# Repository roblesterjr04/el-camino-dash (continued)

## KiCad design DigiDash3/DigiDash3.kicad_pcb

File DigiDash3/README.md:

# DigiDash main board, rev 3: all through-hole

Rev 2 ([`DigiDash2/`](../DigiDash2/)) with every SMD part swapped for a through-hole one, so the board needs **no
assembly service**: order the bare PCB and solder it by hand (about 170 parts, all leaded). Same outline, slot row,
screen headers, mounting and screen holes and rear connector group as rev 2, so the housing fits both. Started
2026-10-26 to get the first set under the fab's assembly fees and the 35 % US duty on assembled boards.

| File | What |
| --- | --- |
| `DigiDash3.kicad_sch` / `.kicad_pcb` / `.kicad_pro` | The board: 329 × 113 mm, **2 layers**, parts on the back, screen headers on the front. KiCad 10 |
| `DigiDash3.pretty/` | The slot socket (numbered to mate with the cards) and a radial PTC footprint, from `generate/gen_footprints.py` |
| `DigiDash3_BOM.csv` | Parts list for hand assembly (`generate/gen_bom.py`): grouped by vendor (DigiKey, then LCSC), with each line's product link and its unit price at quantity 1 where the page showed one (looked up 2026-10-26; `SOURCE` in the generator) |
| `fab/` | Gerbers, drill, placement files (`python3 ../tools/fab_export.py DigiDash3`) |
| `generate/` | The generators, from rev 2's: `gen_sch.py` (schematic), `gen_pcb.py` (placement + Freerouting), `gen_bom.py`, `drc.py` |

**Firmware:** none on the board itself. The three screens run [`firmware/esp32_p4_display`](../firmware/esp32_p4_display/), as on rev 2.

## What changed from rev 2

| Block | Rev 2 (SMD) | Rev 3 (through-hole) |
| --- | --- | --- |
| 5 V | One TPS54560B, 5 A, 400 kHz | **Two LM2576HV-5.0** (TO-220-5 lying flat, 3 A, 52 kHz): U2 feeds the three screens (`+5V_SCR`), U3 feeds the board, the six slots and the cable ports (`+5V`). Each: 100 µF 63 V in, SB560 catch diode, **68 µH** radial inductor (Abracon AIAP-03-680K, 3.3 A: no stocked 100 µH part of 3 A or more fits a 14 mm / 10 mm-pitch footprint, and 68 µH costs about 45 % more ripple current at this load, still continuous), 1000 µF 16 V out (TI SNVS107 figure 1) |
| Enable | EN divider from the ignition, WAKE through a BAT54S | Both bucks' ON/OFF pins on one 2N3904 (Q7): low (on) while the ignition is on (47k) or a card holds WAKE (1N4148 + 10k). Off, the pins rest at 12V_BATT through 100k (ON/OFF may go to VIN) |
| 3.3 V | AP7361C-33 SOT-223 | LD1117V33, TO-220 lying flat, 10 µF electrolytics in and out. Also feeds the video module when JP1 is strapped to 3.3 V |
| 1.8 V | AP2112K-1.8 for the TVP5150 core | Gone with the decoder |
| Reverse / switch FETs | SUD50P04 DPAK ×3 | IRF4905 TO-220 lying flat ×3 (55 V, 20 mΩ), gates clamped by 1N4744A (15 V) |
| TVS | SMCJ33A ×2 | 1.5KE33A (DO-201) ×2 |
| CAN transceivers | MCP2562-E/SN SOIC ×3 | **MCP2562-E/P DIP-8** ×3 (same pins) |
| CAN ESD clamps | NUP2105L SOT-23 ×2 | Two SA24CA bidirectional TVS (DO-15) per site: CANH and CANL to ground |
| Clamps / wake diode | BAT54S ×3 | BAT85 (DO-35) ×4, 1N4148 ×1 |
| PTCs | 1812 / 1206 SMD ×35 | Bourns MF-R radial ×29 (MF-R050, R110, R010, R020; same hold currents, 60 V except the 1.1 A at 30 V) |
| Video | TVP5150AM1 on the board, crystal, RCA input chain | **J8: a 2×10 socket for a TVP5150 breakout module**, JP1 (its VCC: 5 V or 3.3 V), J10 (PCLK / RESET wires). The module carries its own video input, crystal and regulators, so J11 (RCA) and the input chain are gone |
| Termination switch | KingTek SMD | Through-hole 2-way slide DIP (DSWB02LHGET) |
| Passives | 0603 / 0805 / 1210 | 1/4 W axial resistors (7.62 mm), 5 mm disc 100 nF, radial electrolytics |
| Layers | 4 (GND and +5 V planes) | **2**, ground pours on both sides; 0.25 mm tracks, 0.15 mm clearance, 0.6 / 0.3 vias (JLCPCB's 2-layer limit is 0.127 / 0.127); the 5 V feeds at 1.5 mm, 12 V at 1.0 mm. The slot sockets' pads are 1.5 mm on 1.0 mm holes (rev 2: 1.7), so two tracks pass between neighbours: at 0.3 / 0.2 and 1.7 mm pads the router left bus nets open |

Unchanged: J7 / J13 / J9 / J6 / J16 / J27 / J17–J25 and their pin use, the six slot sockets and their pinout
([`accessory_ports.md`](../docs/hardware/accessory_ports.md)), the AUX 12 V path, the sensor-serial fan-out, the
illumination / reverse inputs, the slot ID resistors, WAKE, LAMP / REV levels, the audio bus and I2S rail, and the
screen headers' pin use (`HDR_NETS` in `gen_sch.py`, with `+5V_SCR` on pins 1 and 3).

## The video module socket (J8)

J8's pin order is the module's own, odd pins in one row, even in the other, 1–20:

| Pin | Net | Pin | Net |
| --- | --- | --- | --- |
| 1 | VID_VCC (JP1: 5 V or 3.3 V) | 2 | GND |
| 3 | CL_SCL (cluster I2C) | 4 | CL_SDA |
| 5 | V_VS → J1 pin 24 | 6 | V_HS → J1 pin 30 |
| 7 | n.c. | 8 | n.c. |
| 9 | V_D7 → J1 pin 16 | 10 | V_D6 → J1 pin 32 |
| 11 | V_D5 → J1 pin 35 | 12 | V_D4 → J1 pin 39 |
| 13 | V_D3 → J1 pin 8 | 14 | V_D2 → J1 pin 11 |
| 15 | V_D1 → J1 pin 12 | 16 | V_D0 → J1 pin 14 |
| 17 | n.c. | 18 | V_FID → J1 pin 37 |
| 19 | INT (10k to ground, unused) | 20 | ID (10k to ground, **not fitted**: only if the module wants its address strap here) |

**The module's header has no pixel-clock pin.** The center screen's camera interface needs PCLK (J1 pin 25), so J10
pin 1 carries that net: run a wire from the module's PCLK point (a test pad or the decoder's SCLK pin) to J10 pin 1.
J10 pin 2 is the center screen's reset line (GPIO52, J1 pin 36) for the module's RESET if it has one; pin 3 is GND.
Check the module's supply before strapping JP1: most TVP5150 breakouts take 3.3 V. Fit a **female** 2×10 socket at
J8 (the module carries the pins; the BOM says so).

## Board

- **Sides:** every part's body is on the back; only the three screen headers are on the front. Soldering is from
  the front (the pin tails come through there), so the screens come off first.
- **Heights on the back, outside the cards:** rev 2's housing allowed about 10.5 mm over the power section. Rev 3's
  power parts are taller: the inductors (Abracon AIAP-03-680K, 11.4 mm across) stand **23 mm**, the tallest parts on the board; the 1000 µF output caps (Rubycon 16YXJ1000MT810X16) 16 mm;
  the 100 µF caps 12.5 mm; the radial PTCs 8–9 mm; the TO-220s lying flat about 5 mm; the DIP transceivers 4 mm. The
  video module on J8 stands about 12 mm plus its own height. **The housing's power-section step needs to grow to
  about 25 mm over the two inductors (18 mm elsewhere)**, and the module's footprint (about 40 × 30 mm, at x 190–220, y 60–80) needs room behind J8.
- **Under the cards** (7 mm limit) only lying-flat resistors, diodes, DIPs and TO-92s go; the placer keeps the tall
  parts out of the card envelopes (`TALL_RE` in `gen_pcb.py`).
- **Placement:** slots, screen headers, holes and the rear connector group as rev 2 (`SLOTS`, `SCREENS`, `HOLES_MH`,
  `GROUP`). The two bucks lie flat at x 170, y 44 and 60, pins toward the slots; Q5 and the LDO east of them; the
  video socket below the power section at (205, 69); the transceivers beside their headers.

## Status

**Schematic: done** (168 parts, 2026-10-26). **PCB: placed, routed and DRC-clean** (2026-10-26): Freerouting at
150 passes, 2083 tracks and vias, then **two links drawn by hand** that the finisher would not make because they end
on the net ties' pads (its clearance check keeps everything off a tie): AUDIO_GND from its F.Cu run at y 63.42 up to
NT2 pad 2 (91.75, 61.85), and AUX_GND on B.Cu, 1.0 mm, from (249.65, 64.0) down to NT1 pad 2 (249.65, 71.5).
**A regeneration drops those two** (re-add them, or check the DRC's two unconnected items). DRC: 0 errors; the
expected warnings are the two library-mismatch notes and two silkscreen overlaps. Fab files exported. The inductors' leads are bent out to the 10 mm pads (the Abracon's own pitch is narrower); the body sits
above the pads. Not yet checked: the LM2576 layout by eye (each buck's input cap,
catch diode and inductor should sit tight round its pins), the housing against the heights above, and the module's
PCLK / RESET / VCC against the actual breakout.

## Regenerating

KiCad 10, numpy in KiCad's python, Freerouting 1.9.0 (the jar in `../DigiDash2/generate/`) on Java 17+:

```bash
KIPY=/Applications/KiCad/KiCad.app/Contents/Frameworks/Python.framework/Versions/Current/bin/python3
python3 generate/gen_footprints.py && python3 generate/gen_sch.py   # also writes generate/refs.json
JAVA=/opt/homebrew/opt/openjdk@17/bin/java FR_PASSES=60 $KIPY generate/gen_pcb.py --route ../DigiDash2/generate/freerouting-1.9.0.jar
python3 generate/drc.py && $KIPY generate/gen_bom.py && python3 ../tools/fab_export.py DigiDash3
```

With no planes there is no fan-out or stitching step: Freerouting routes GND like any other net, and the ground pours
are filled afterwards. `--from-ses`, `--finish`, `--fill` and `--labels` work as on rev 2. Do not set `DIGIDASH_RIPUP=1`
on this board: the rip-up finisher cascaded for over an hour without ending (2026-10-26).

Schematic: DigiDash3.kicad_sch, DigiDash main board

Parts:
C1, C3, C5, C10: 100u 63V; CP_Radial_D10.0mm_P5.00mm
C2, C9, C11, C12, C13, C14, C15, C16, C17, C18, C19, C20, C21: 100n; C_Disc_D5.0mm_W2.5mm_P5.00mm
C4, C6: 1000u 16V; CP_Radial_D10.0mm_P5.00mm
C7, C8: 10u 25V; CP_Radial_D5.0mm_P2.00mm
D4, D8, D9: 1N4744A; D_DO-41_SOD81_P10.16mm_Horizontal
D5, D10: 1.5KE33A; D_DO-201AD_P15.24mm_Horizontal
D6, D7: SB560; D_DO-201AD_P15.24mm_Horizontal
D11, D12, D13, D14: SA24CA; D_DO-15_P10.16mm_Horizontal
D15: 1N4148; D_DO-35_SOD27_P7.62mm_Horizontal
D16, D17, D18, D19: BAT85; D_DO-35_SOD27_P7.62mm_Horizontal
F1: 5A mini blade; Fuseholder_Blade_Mini_Keystone_3568
F2, F4, F5, F6, F7, F9, F10, F13, F14, F17, F18, F21, F22, F25, F26, F29, F30: PTC 0.5A; PTC_Radial_P5.08mm
F3, F11, F15, F19, F23, F27, F31: PTC 0.1A; PTC_Radial_P5.08mm
F8: PTC 1.1A; PTC_Radial_P5.08mm
F12, F16, F20, F24, F28, F32: PTC 0.2A; PTC_Radial_P5.08mm
H1, H2, H3, H4: MountingHole; MountingHole_3.2mm_M3_Pad
J1: Center Screen - Master; PinHeader_2x20_P2.54mm_Vertical
J4: Right Screen; PinHeader_2x20_P2.54mm_Vertical
J5: Left Screen; PinHeader_2x20_P2.54mm_Vertical
J6: Serial; JST_PH_B4B-PH-K_1x04_P2.00mm_Vertical
J7: Vehicle power; Molex_Micro-Fit_3.0_43650-0615_1x06_P3.00mm_Vertical
J8: Video module; PinHeader_2x10_P2.54mm_Vertical
J9: Backup Camera; JST_PH_B4B-PH-K_1x04_P2.00mm_Vertical
J10: Video aux; PinHeader_1x03_P2.54mm_Vertical
J13: AUX 12V in; Molex_Mini-Fit_Jr_5566-02A_2x01_P4.20mm_Vertical
J16: CAN debug; PinHeader_1x03_P2.54mm_Vertical
J17: Cable port 1; JST_PH_B4B-PH-K_1x04_P2.00mm_Vertical
J22: Cable port 2; JST_PH_B4B-PH-K_1x04_P2.00mm_Vertical
J23: Cable port 3; JST_PH_B4B-PH-K_1x04_P2.00mm_Vertical
J24: Cable port 4; JST_PH_B4B-PH-K_1x04_P2.00mm_Vertical
J25: Trunk port; Molex_Micro-Fit_3.0_43650-0415_1x04_P3.00mm_Vertical
J27: Sensor serial in; PinHeader_1x02_P2.54mm_Vertical
J31: Slot 1; Slot_Socket_2x15_P2.54mm_Vertical
J32: Slot 2; Slot_Socket_2x15_P2.54mm_Vertical
J33: Slot 3; Slot_Socket_2x15_P2.54mm_Vertical
J34: Slot 4; Slot_Socket_2x15_P2.54mm_Vertical
J35: Slot 5; Slot_Socket_2x15_P2.54mm_Vertical
J36: Slot 6; Slot_Socket_2x15_P2.54mm_Vertical
JP1: Video VCC; PinHeader_1x03_P2.54mm_Vertical
L1, L2: 68u; L_Radial_D14.2mm_P10.00mm_Neosid_SD14
NT1, NT2: NetTie; NetTie-2_THT_Pad1.0mm
Q1, Q3, Q4, Q7: 2N3904; TO-92_Inline
Q2, Q5, Q6: IRF4905; TO-220-3_Horizontal_TabDown
R1, R5, R6, R9, R10, R13, R14, R15, R20, R21, R22, R23, R24, R26, R28, R30: 10k; R_Axial_DIN0207_L6.3mm_D2.5mm_P7.62mm_Horizontal
R2, R38, R39, R41: 100k; R_Axial_DIN0207_L6.3mm_D2.5mm_P7.62mm_Horizontal
R3, R37: 47k; R_Axial_DIN0207_L6.3mm_D2.5mm_P7.62mm_Horizontal
R4, R8, R36: 22k; R_Axial_DIN0207_L6.3mm_D2.5mm_P7.62mm_Horizontal
R7, R18, R19: 4.7k; R_Axial_DIN0207_L6.3mm_D2.5mm_P7.62mm_Horizontal
R11, R12, R32: 1k; R_Axial_DIN0207_L6.3mm_D2.5mm_P7.62mm_Horizontal
R16, R17: 120; R_Axial_DIN0207_L6.3mm_D2.5mm_P7.62mm_Horizontal
R25, R27, R29: 20k; R_Axial_DIN0207_L6.3mm_D2.5mm_P7.62mm_Horizontal
R31: 10k; R_Axial_DIN0207_L6.3mm_D2.5mm_P7.62mm_Horizontal; not fitted
R33: 3.3k; R_Axial_DIN0207_L6.3mm_D2.5mm_P7.62mm_Horizontal
R34: 6.8k; R_Axial_DIN0207_L6.3mm_D2.5mm_P7.62mm_Horizontal
R35: 12k; R_Axial_DIN0207_L6.3mm_D2.5mm_P7.62mm_Horizontal
R40, R42: 27k; R_Axial_DIN0207_L6.3mm_D2.5mm_P7.62mm_Horizontal
SW1: TERM; SW_DIP_SPSTx02_Slide_6.7x6.64mm_W7.62mm_P2.54mm_LowProfile
U2, U3: LM2576HVT-5.0; TO-220-5_Horizontal_TabDown
U5, U9, U10: MCP2562-E/P; DIP-8_W7.62mm
U11: LD1117V33; TO-220-3_Horizontal_TabDown

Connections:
+3V3: C8.1, C9.1, C12.1, C14.1, C16.1, D16.1 (K), D18.1 (K), F3.1, F11.1, F15.1, F19.1, F23.1, F27.1, F31.1, JP1.3, R13.1, R14.1, R15.1, R18.1, R19.1, U5.5 (Vio), U9.5 (Vio), U10.5 (Vio), U11.2 (VO)
+5V: C6.1, C7.1, C11.1, C13.1, C15.1, F4.1, F5.1, F6.1, F7.1, F9.1, F13.1, F17.1, F21.1, F25.1, F29.1, JP1.1, L2.2, U3.4 (FB), U5.3 (VDD), U9.3 (VDD), U10.3 (VDD), U11.3 (VI)
/3V3_R: J4.18, R12.2
/12V_BATT: C1.1, C2.1, C3.1, C5.1, D4.1 (K), D5.1 (A1), D8.1 (K), F12.1, F16.1, F20.1, F24.1, F28.1, F32.1, Q2.3 (S), Q5.3 (S), R2.1, R6.1, U2.1 (VIN), U3.1 (VIN)
/+5V_SCR: C4.1, J1.1, J1.3, J4.1, J4.3, J5.1, J5.3, L1.2, U2.4 (FB)
/AUDIO_GND: J31.23, J32.23, J33.23, J34.23, J35.23, J36.23, NT2.2 (B)
/AUDIO_L: J31.21, J32.21, J33.21, J34.21, J35.21, J36.21
/AUDIO_R: J31.22, J32.22, J33.22, J34.22, J35.22, J36.22
/AUX12: C10.1, D9.1 (K), D10.1 (A1), J31.25, J31.26, J31.27, J32.25, J32.26, J32.27, J33.25, J33.26, J33.27, J34.25, J34.26, J34.27, J35.25, J35.26, J35.27, J36.25, J36.26, J36.27, Q6.3 (S)
/AUX_GND: C10.2, D10.2 (A2), J13.2, J31.28, J31.29, J31.30, J32.28, J32.29, J32.30, J33.28, J33.29, J33.30, J34.28, J34.29, J34.30, J35.28, J35.29, J35.30, J36.28, J36.29, J36.30, NT1.2 (B), R10.2
/AUX_IN: F1.1, J13.1
/AUX_IN_F: F1.2, Q6.2 (D)
/BATT_IN: J7.1, J7.2, Q2.2 (D)
/BUCK_ONOFF: Q7.3 (C), R2.2, U2.5 (~ON/OFF), U3.5 (~ON/OFF)
/C1_5V: F4.2, J17.1
/C2_5V: F5.2, J22.1
/C3_5V: F6.2, J23.1
/C4_5V: F7.2, J24.1
/CAM_12V: F2.2, J9.2
/CANH: D11.1 (A1), D13.1 (A1), J16.1, J17.2, J22.2, J23.2, J24.2, J25.1, J31.5, J32.5, J33.5, J34.5, J35.5, J36.5, R16.1, R17.1, U5.7 (CANH), U9.7 (CANH), U10.7 (CANH)
/CANL: D12.1 (A1), D14.1 (A1), J16.2, J17.3, J22.3, J23.3, J24.3, J25.2, J31.6, J32.6, J33.6, J34.6, J35.6, J36.6, R16.2, SW1.4, U5.6 (CANL), U9.6 (CANL), U10.6 (CANL)
/CAN_RX_C: J1.23, U9.4 (RXD)
/CAN_RX_L: J5.23, U5.4 (RXD)
/CAN_RX_R: J4.23, U10.4 (RXD)
/CAN_TERM_R: R17.2, SW1.1
/CAN_TX_C: J1.31, R14.2, U9.1 (TXD)
/CAN_TX_L: J5.31, R13.2, U5.1 (TXD)
/CAN_TX_R: J4.31, R15.2, U10.1 (TXD)
/CL_SCL: J1.34, J4.34, J5.34, J8.3, R19.2
/CL_SDA: J1.38, J4.38, J5.38, J8.4, R18.2
/I2S_BCK: J31.15, J32.15, J33.15, J34.15, J35.15, J36.15
/I2S_MCLK: J31.24, J32.24, J33.24, J34.24, J35.24, J36.24
/I2S_MIC: J31.17, J32.17, J33.17, J34.17, J35.17, J36.17
/I2S_RET: J31.18, J32.18, J33.18, J34.18, J35.18, J36.18
/I2S_WS: J31.16, J32.16, J33.16, J34.16, J35.16, J36.16
/IGN_IN: J7.5, R3.1, R8.1
/ILLUM_IN: J7.6, R20.1, R39.1
/Illumination: C17.1, J1.28, Q1.3 (C)
/LAMP_LVL: C20.1, D16.2 (A), D17.1 (K), J31.13, J32.13, J33.13, J34.13, J35.13, J36.13, R39.2, R40.1
/POS_L: J5.17, R11.1
/POS_R: J4.17, R12.1
/Q1_B: Q1.2 (B), R20.2, R21.1
/Q2_G: D4.2 (A), Q2.1 (G), R1.1
/Q3_B: Q3.2 (B), R22.2, R23.1
/Q4_B: Q4.2 (B), R8.2, R9.1
/Q4_C: Q4.3 (C), R7.2
/Q5_G: D8.2 (A), Q5.1 (G), R6.2, R7.1
/Q6_G: D9.2 (A), Q6.1 (G), R10.1
/Q7_B: Q7.2 (B), R3.2, R4.1, R5.2
/REV_IN: J9.1, R22.1, R41.1
/REV_LVL: C21.1, D18.2 (A), D19.1 (K), J31.14, J32.14, J33.14, J34.14, J35.14, J36.14, R41.2, R42.1
/REV_TRIGGER: C18.1, J1.27, Q3.3 (C)
/S1_3V3: F11.2, J31.9
/S1_5V: F9.2, J31.1, J31.2
/S1_12V: F10.2, J31.8
/S1_BATT: F12.2, J31.10
/S1_ID: J31.11, R32.1
/S2_3V3: F15.2, J32.9
/S2_5V: F13.2, J32.1, J32.2
/S2_12V: F14.2, J32.8
/S2_BATT: F16.2, J32.10
/S2_ID: J32.11, R33.1
/S3_3V3: F19.2, J33.9
/S3_5V: F17.2, J33.1, J33.2
/S3_12V: F18.2, J33.8
/S3_BATT: F20.2, J33.10
/S3_ID: J33.11, R34.1
/S4_3V3: F23.2, J34.9
/S4_5V: F21.2, J34.1, J34.2
/S4_12V: F22.2, J34.8
/S4_BATT: F24.2, J34.10
/S4_ID: J34.11, R35.1
/S5_3V3: F27.2, J35.9
/S5_5V: F25.2, J35.1, J35.2
/S5_12V: F26.2, J35.8
/S5_BATT: F28.2, J35.10
/S5_ID: J35.11, R36.1
/S6_3V3: F31.2, J36.9
/S6_5V: F29.2, J36.1, J36.2
/S6_12V: F30.2, J36.8
/S6_BATT: F32.2, J36.10
/S6_ID: J36.11, R37.1
/SENS_TX: J27.1, R24.1, R26.1, R28.1
/SENS_TX_C: J1.15, R26.2, R27.1
/SENS_TX_L: J5.15, R24.2, R25.1
/SENS_TX_R: J4.15, R28.2, R29.1
/SER_3V3: F3.2, J6.1
/SER_RX: J1.20, J6.3
/SER_TX: J1.22, J6.2
/SW12: F2.1, F8.1, F10.1, F14.1, F18.1, F22.1, F26.1, F30.1, Q5.2 (D)
/SW_A: D6.1 (K), L1.1, U2.2 (OUT)
/SW_B: D7.1 (K), L2.1, U3.2 (OUT)
/TRUNK_12V: F8.2, J25.3
/VID_ID: J8.20, R31.1
/VID_INT: J8.19, R30.1
/VID_VCC: C19.1, J8.1, JP1.2
/V_D0: J1.14, J8.16
/V_D1: J1.12, J8.15
/V_D2: J1.11, J8.14
/V_D3: J1.8, J8.13
/V_D4: J1.39, J8.12
/V_D5: J1.35, J8.11
/V_D6: J1.32, J8.10
/V_D7: J1.16, J8.9
/V_FID: J1.37, J8.18
/V_HS: J1.30, J8.6
/V_P17: J1.36, J10.2
/V_PCLK: J1.25, J10.1
/V_VS: J1.24, J8.5
/WAKE: D15.2 (A), J31.12, J32.12, J33.12, J34.12, J35.12, J36.12, R38.1
/WAKE_K: D15.1 (K), R5.1
GND: C1.2, C2.2, C3.2, C4.2, C5.2, C6.2, C7.2, C8.2, C9.2, C11.2, C12.2, C13.2, C14.2, C15.2, C16.2, C17.2, C18.2, C19.2, C20.2, C21.2, D5.2 (A2), D6.2 (A), D7.2 (A), D11.2 (A2), D12.2 (A2), D13.2 (A2), D14.2 (A2), D17.2 (A), D19.2 (A), H1.1, H2.1, H3.1, H4.1, J1.5, J1.10, J1.13, J1.26, J1.29, J1.33, J1.40, J4.5, J4.10, J4.13, J5.5, J5.10, J5.13, J5.19, J5.26, J5.29, J5.33, J5.40, J6.4, J7.3, J7.4, J8.2, J9.4, J10.3, J16.3, J17.4, J22.4, J23.4, J24.4, J25.4, J27.2, J31.3, J31.4, J31.7, J31.19, J31.20, J32.3, J32.4, J32.7, J32.19, J32.20, J33.3, J33.4, J33.7, J33.19, J33.20, J34.3, J34.4, J34.7, J34.19, J34.20, J35.3, J35.4, J35.7, J35.19, J35.20, J36.3, J36.4, J36.7, J36.19, J36.20, NT1.1 (A), NT2.1 (A), Q1.1 (E), Q3.1 (E), Q4.1 (E), Q7.1 (E), R1.2, R4.2, R9.2, R11.2, R21.2, R23.2, R25.2, R27.2, R29.2, R30.2, R31.2, R32.2, R33.2, R34.2, R35.2, R36.2, R37.2, R38.2, R40.2, R42.2, U2.3 (GND), U3.3 (GND), U5.2 (VSS), U5.8 (STBY), U9.2 (VSS), U9.8 (STBY), U10.2 (VSS), U10.8 (STBY), U11.1 (GND)

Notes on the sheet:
DIGIDASH MAIN BOARD, REV 3 - all through-hole (no assembly service): rev 2 (DigiDash2/) with the SMD parts swapped for through-hole ones, two 3 A bucks in place of the 5 A one, and the video decoder on a plug-in module
Same outline, slot row, screen headers, holes and rear connector group as rev 2 (the housing fits both). The video section is a 2x10 socket (J8) for a TVP5150 breakout module; CAN transceivers are the DIP MCP2562-E/P. Two layers.
POWER: J7 (battery, ignition, illumination), reverse protection, TVS, two LM2576HV 3 A bucks (U2: the three screens, U3: everything else), a 3.3 V LDO, switched 12 V
Two LM2576HV-5.0 (TI SNVS107 figure 1, 100 uH / 1000 uF / 5 A Schottky each): U2 feeds the three screens (+5V_SCR), U3 feeds the board, the slots and the cable ports (+5V). Both ON/OFF pins hang on Q7: low (on) while the ignition is on or a card holds WAKE high. Off, the pins rest at 12V_BATT throu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
SW12 (switched 12 V for the slots' pin 8, the trunk port and the camera): a P-FET high-side switch from 12V_BATT, on while the ignition is on.
AUX 12 V: slot power from its own fused feed (pins 25-30 of every slot). Its return (AUX_GND) meets GND only at NT1.
SCREENS: J5 left, J1 center, J4 right (ESP32-P4, plugged in face down), 5 V from U2. One MCP2562 (DIP) each, VIO from the board 3.3 V. 120 R at the left (R) and right (switched) ends of the bus.
Vehicle inputs to the screens (as rev 1): illumination (J7 pin 6), reverse (J9 pin 1). J6: serial port (center UART2).
Sensor serial (optional, a jumper wire from the sensor card): J27 pin 1 (5 V TX) -> 10k / 20k divider per screen (5 V -> 3.3 V) -> pin 15 of J5 / J1 / J4. Sensor data normally arrives on CAN; this is the fallback path.
VIDEO: a TVP5150 breakout module on J8 (2x10 socket; the module carries its own video input, crystal and regulators) -> 8-bit BT.656 to the center screen's camera pins (same J1 pins as rev 1 and 2). I2C on the cluster bus. JP1 straps the module's VCC to 5 V or 3.3 V. J10 brings PCLK / RESET on wire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
J8 pin order is the module's: 1 VCC, 2 GND, 3 SCL, 4 SDA, 5 VSYNC, 6 HSYNC, 7-8 n.c., 9-16 D7..D0, 17 n.c., 18 FID, 19 INT, 20 ID. The module has no pixel-clock pin on its header: J10 pin 1 is the center screen's PCLK (J1 pin 25), for a wire from the module's PCLK point; J10 pin 2 is the center's r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
CABLE PORTS J17, J22, J23, J24 (JST PH). Trunk port J25 (bus extension, 12 V).
SLOTS: six 2x15 sockets J31-J36 (slot 1-6), cards stand on edge (docs/hardware/accessory_ports.md). Per slot: fused 5 V, switched 12 V, 3.3 V, constant 12 V, an ID resistor. Shared: CAN, WAKE, LAMP / REV levels, the analog audio bus, AUX 12 V, and the I2S rail (BCK, WS, MIC, RET, MCLK: bused to all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
WAKE: a card drives it high (about 3.3 V, through its own diode) to start or hold the 5 V rails with the key off (the sensor card holds it to finish after key-off). LAMP_LVL / REV_LVL: J7 pin 6 and J9 pin 1 scaled to 0-3.3 V.

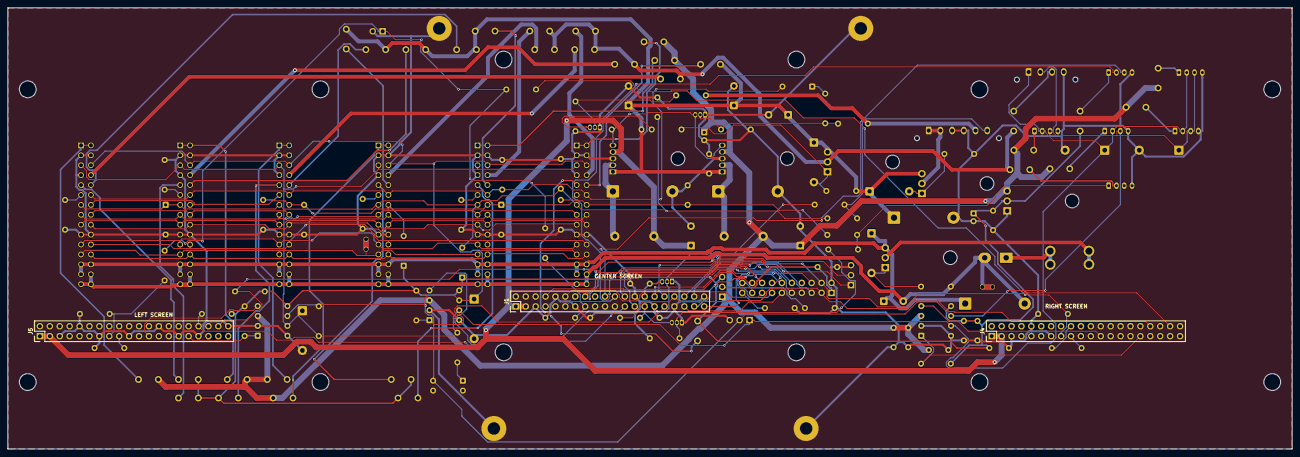
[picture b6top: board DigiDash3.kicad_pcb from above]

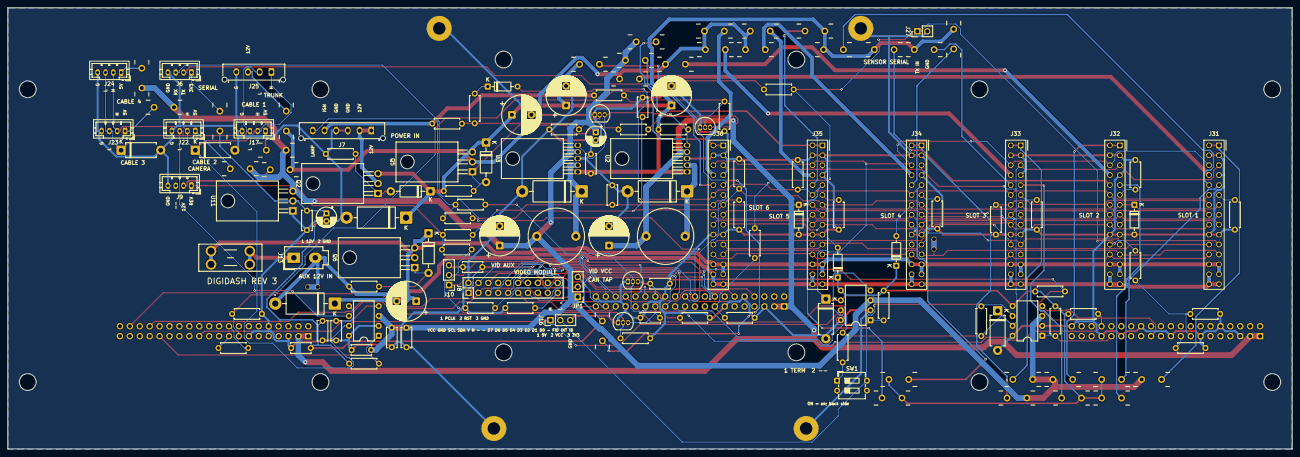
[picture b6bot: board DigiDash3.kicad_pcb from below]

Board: 2 copper layers, 329.0 x 113.0 mm, 168 parts (153 on the bottom side), 112 nets.

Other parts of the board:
H5, H6, H7, H8, H9, H10, H11, H12, H13, H14, H15, H16: M4 screen; MountingHole_4.3mm_M4

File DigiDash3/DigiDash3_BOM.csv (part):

Item #,Vendor,Designator,Qty,Manufacturer,Mfg Part #,Vendor link,"Unit price (qty 1, $)",Line ($),Description / Value,Package/Footprint,Type,Side,Your Instructions / Notes
1,DigiKey,C1 C3 C5 C10,4,Nichicon,UPW1J101MPD,https://www.digikey.com/en/products/detail/nichicon/UPW1J101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,,,"100u 63V: Aluminium electrolytic 100 uF 63 V, radial 10 x 12.5 mm, 5 mm pitch",radial,THT,Bottom,"LCSC alternative: Rubycon 63YXF100MFFC10X12.5, C388845"
2,DigiKey,C2 C9 C11 C12 C13 C14 C15 C16 C17 C18 C19 C20 C21,13,Vishay,K104K15X7RF5TL2,https://www.digikey.com/en/products/detail/vishay-beyschlag-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,,,"100n: Ceramic 100 nF X7R 50 V, 5 mm pitch",radial,THT,Bottom,"DigiKey lists 2.5 mm lead spacing: confirm the 5 mm (F5) version, the footprint is 5 mm"
3,DigiKey,C7 C8,2,Rubycon,50YXJ10M5X11,https://www.digikey.com/en/products/detail/rubycon/50YXJ10M5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,,,"10u 25V: Aluminium electrolytic 10 uF 50 V, radial 5 x 11 mm, 2 mm pitch",radial,THT,Bottom,
4,DigiKey,D4 D8 D9,3,onsemi,1N4744A,https://www.digikey.com/en/products/detail/onsemi/1N4744A/977267,0.27,0.81,"1N4744A: Zener 15 V 1 W, DO-41",axial,THT,Bottom,
5,DigiKey,D5 D10,2,Littelfuse,1.5KE33A,https://www.digikey.com/en/products/detail/littelfuse-inc/1-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,,,"1.5KE33A: TVS 33 V standoff, unidirectional, 1500 W, DO-201",axial,THT,Bottom,
6,DigiKey,D6 D7,2,Vishay,SB560-E3/54,https://www.digikey.com/en/products/detail/vishay-general-se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,,,"SB560: Schottky 5 A 60 V, DO-201AD (1N5822 fits too)",axial,THT,Bottom,
7,DigiKey,D11 D12 D13 D14,4,Littelfuse,SA24CA,https://www.digikey.com/en/products/detail/littelfuse-inc/SA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,0.30,1.20,"SA24CA: TVS 24 V bidirectional, 500 W, DO-15 (CAN clamp)",axial,THT,Bottom,
8,DigiKey,D15,1,onsemi,1N4148,https://www.digikey.com/en/products/detail/onsemi/1N4148/458603,0.10,0.10,"1N4148: Signal diode, DO-35",axial,THT,Bottom,
9,DigiKey,D16 D17 D18 D19,4,Vishay,BAT85S-TAP,https://www.digikey.com/en/products/detail/vishay-general-se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,0.14,0.56,"BAT85: Schottky 200 mA 30 V, DO-35",axial,THT,Bottom,
10,DigiKey,F1,1,Keystone,3568,https://www.digikey.com/en/products/detail/keystone-electron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,,,"5A mini blade: Fuse holder, mini blade (ATM), PCB",THT,THT,Bottom,Holder only; fit a 5 A mini blade fuse (Littelfuse 0297005.WXNV)
11,DigiKey,F2 F4 F5 F6 F7 F9 F10 F13 F14 F17 F18 F21 F22 F25 F26 F29 F30,17,Bourns,MF-R050,https://www.digikey.com/en/products/detail/bourns-inc/MF-R05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,,,"PTC 0.5A: PTC 0.5 A hold, 60 V, radial",radial,THT,Bottom,
12,DigiKey,F3 F11 F15 F19 F23 F27 F31,7,Bourns,MF-R010,https://www.digikey.com/en/products/detail/bourns-inc/MF-R01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,,,"PTC 0.1A: PTC 0.1 A hold, 60 V, radial",radial,THT,Bottom,
13,DigiKey,F8,1,Bourns,MF-R110,https://www.digikey.com/en/products/detail/bourns-inc/MF-R11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,0.47,0.47,"PTC 1.1A: PTC 1.1 A hold, 30 V, radial",radial,THT,Bottom,
14,DigiKey,F12 F16 F20 F24 F28 F32,6,Bourns,MF-R020,https://www.digikey.com/en/products/detail/bourns-inc/MF-R02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,,,"PTC 0.2A: PTC 0.2 A hold, 60 V, radial",radial,THT,Bottom,On the battery line
15,DigiKey,J1,1,Sullins,PRPC020DAAN-RC,https://www.digikey.com/en/products/detail/sullins-connector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,1.34,1.34,"Center Screen - Master: Pin header 2 x 20, 2.54 mm, vertical (male; the screen has the 40-pin socket)",THT 2x20,THT,Top,"FRONT side (screen side), the only parts on the front"
16,DigiKey,J4,1,Sullins,PRPC020DAAN-RC,https://www.digikey.com/en/products/detail/sullins-connector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,1.34,1.34,"Right Screen: Pin header 2 x 20, 2.54 mm, vertical (male; the screen has the 40-pin socket)",THT 2x20,THT,Top,"FRONT side (screen side), the only parts on the front"
17,DigiKey,J5,1,Sullins,PRPC020DAAN-RC,https://www.digikey.com/en/products/detail/sullins-connector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,1.34,1.34,"Left Screen: Pin header 2 x 20, 2.54 mm, vertical (male; the screen has the 40-pin socket)",THT 2x20,THT,Top,"FRONT side (screen side), the only parts on the front"
18,DigiKey,J6,1,JST,B4B-PH-K-S(LF)(SN),https://www.digikey.com/en/products/detail/jst-sales-america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,0.24,0.24,"Serial: JST PH header, 4 pin, vertical",THT,THT,Bottom,
19,DigiKey,J7,1,Molex,43650-0615,https://www.digikey.com/en/products/detail/molex/0436500615/283465,1.57,1.57,"Vehicle power: Micro-Fit 3.0 header, 6 pin, 1 row, vertical",THT,THT,Bottom,
20,DigiKey,J8,1,Sullins,PPTC102LFBN-RC,https://www.digikey.com/en/products/detail/sullins-connector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,1.16,1.16,"Video module: Socket 2 x 10, 2.54 mm, female, vertical, 8.5 mm (the module plugs in)",THT 2x10,THT,Bottom,"Fit a FEMALE socket here, not a pin header: the module carries the pins"
21,DigiKey,J9,1,JST,B4B-PH-K-S(LF)(SN),https://www.digikey.com/en/products/detail/jst-sales-america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,0.24,0.24,"Backup Camera: JST PH header, 4 pin, vertical",THT,THT,Bottom,
22,DigiKey,J10,1,Sullins,PRPC003SAAN-RC,https://www.digikey.com/en/products/detail/sullins-connector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,0.32,0.32,"Video aux: Pin header 1 x 3, 2.54 mm, vertical",THT 1x3,THT,Bottom,"Wires to the module: PCLK, RESET"
23,DigiKey,J13,1,Molex,39-28-1023,https://www.digikey.com/en/products/detail/molex/0039281023/61397,0.49,0.49,"AUX 12V in: Mini-Fit Jr header 5566-02A, 2 pin, vertical, no pegs",THT,THT,Bottom,
24,DigiKey,J16,1,Sullins,PRPC003SAAN-RC,https://www.digikey.com/en/products/detail/sullins-connector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,0.32,0.32,"CAN debug: Pin header 1 x 3, 2.54 mm, vertical",THT 1x3,THT,Bottom,
25,DigiKey,J17,1,JST,B4B-PH-K-S(LF)(SN),https://www.digikey.com/en/products/detail/jst-sales-america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,0.24,0.24,"Cable port 1: JST PH header, 4 pin, vertical",THT,THT,Bottom,
26,DigiKey,J22,1,JST,B4B-PH-K-S(LF)(SN),https://www.digikey.com/en/products/detail/jst-sales-america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,0.24,0.24,"Cable port 2: JST PH header, 4 pin, vertical",THT,THT,Bottom,
27,DigiKey,J23,1,JST,B4B-PH-K-S(LF)(SN),https://www.digikey.com/en/products/detail/jst-sales-america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,0.24,0.24,"Cable port 3: JST PH header, 4 pin, vertical",THT,THT,Bottom,
28,DigiKey,J24,1,JST,B4B-PH-K-S(LF)(SN),https://www.digikey.com/en/products/detail/jst-sales-america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,0.24,0.24,"Cable port 4: JST PH header, 4 pin, vertical",THT,THT,Bottom,
29,DigiKey,J25,1,Molex,43650-0415,https://www.digikey.com/en/products/detail/molex/0436500415/283463,0.84,0.84,"Trunk port: Micro-Fit 3.0 header, 4 pin, 1 row, vertical",THT,THT,Bottom,
30,DigiKey,J27,1,Sullins,PRPC002SAAN-RC,https://www.digikey.com/en/products/detail/sullins-connector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,0.30,0.30,"Sensor serial in: Pin header 1 x 2, 2.54 mm, vertical",THT 1x2,THT,Bottom,"LCSC alternative: XFCN PZ254V-11-02P, C492401"
31,DigiKey,JP1,1,Sullins,PRPC003SAAN-RC,https://www.digikey.com/en/products/detail/sullins-connector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,0.32,0.32,"Video VCC: Pin header 1 x 3, 2.54 mm, vertical, plus a shunt",THT 1x3,THT,Bottom,"Shunt 1-2 = 5 V, 2-3 = 3.3 V. LCSC alternative: XFCN PZ254V-11-03P, C2937625"
32,DigiKey,Q1 Q3 Q4 Q7,4,onsemi,2N3904BU,https://www.digikey.com/en/products/detail/onsemi/2N3904BU/1413,0.29,1.16,"2N3904: NPN 40 V, TO-92 (E B C)",TO-92,THT,Bottom,
33,DigiKey,Q2 Q5 Q6,3,Infineon,IRF4905PBF,https://www.digikey.com/en/products/detail/infineon-technolo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,2.53,7.59,"IRF4905: P-MOSFET 55 V, 20 mOhm, TO-220 lying flat",TO-220,THT,Bottom,
34,DigiKey,R1 R5 R6 R9 R10 R13 R14 R15 R20 R21 R22 R23 R24 R26 R28 R30,16,Yageo,MFR-25FBF52-10K,https://www.digikey.com/en/products/detail/yageo/MFR-25FBF52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,0.10,1.60,"10k: Resistor 10k 1%, 1/4 W metal film, axial",axial,THT,Bottom,
35,DigiKey,R2 R38 R39 R41,4,Yageo,MFR-25FBF52-100K,https://www.digikey.com/en/products/detail/yageo/MFR-25FBF52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,0.10,0.40,"100k: Resistor 100k 1%, 1/4 W metal film, axial",axial,THT,Bottom,
36,DigiKey,R3 R37,2,Yageo,MFR-25FRF52-47K,https://www.digikey.com/en/products/detail/yageo/MFR-25FRF52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,0.10,0.20,"47k: Resistor 47k 1%, 1/4 W metal film, axial",axial,THT,Bottom,
37,DigiKey,R4 R8 R36,3,Yageo,MFR-25FRE52-22K,https://www.digikey.com/en/products/detail/yageo/MFR-25FRE52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,0.10,0.30,"22k: Resistor 22k 1%, 1/4 W metal film, axial",axial,THT,Bottom,
38,DigiKey,R7 R18 R19,3,Yageo,MFR-25FBF52-4K7,https://www.digikey.com/en/products/result?keywords=MFR-25FBF52-4K7,0.10,0.30,"4.7k: Resistor 4.7k 1%, 1/4 W metal film, axial",axial,THT,Bottom,
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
